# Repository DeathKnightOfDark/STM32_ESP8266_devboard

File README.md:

# STM32_ESP8266_devboard
Devboard, based on STM32 and ESP8266

This project about devboard, based on STM32F103C8T6 and ESP8266. They are connected with UART

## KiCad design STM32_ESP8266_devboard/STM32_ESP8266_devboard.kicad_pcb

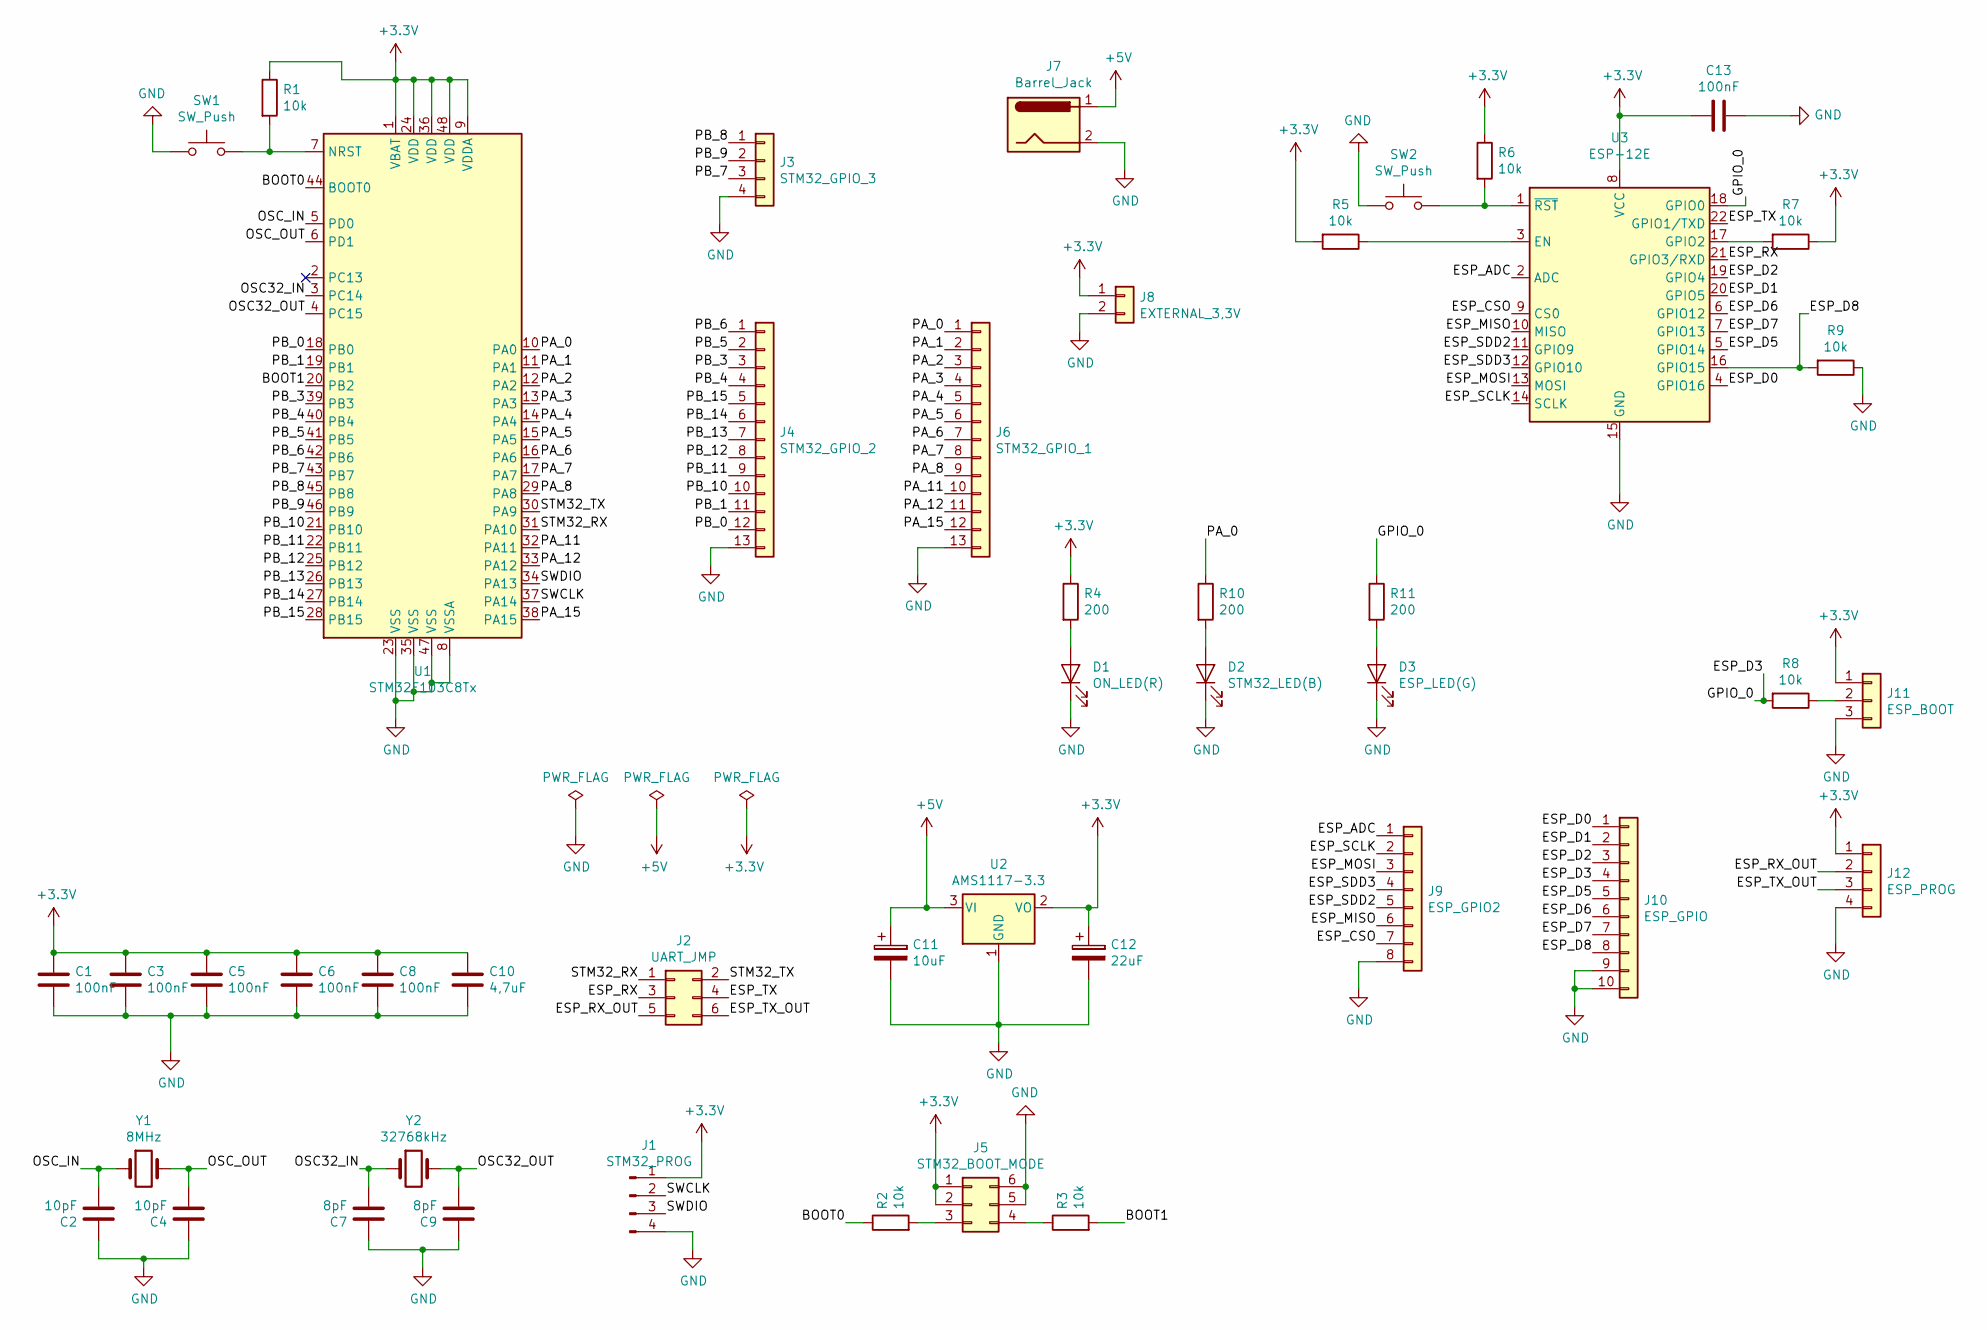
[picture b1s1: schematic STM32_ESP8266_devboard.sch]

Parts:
C1, C3, C5, C6, C8, C13: 100nF; C_0805_2012Metric
C2, C4: 10pF; C_0805_2012Metric
C7, C9: 8pF; C_0805_2012Metric
C10: 4,7uF; C_0805_2012Metric
C11: 10uF; CP_Radial_D5.0mm_P2.50mm
C12: 22uF; CP_Radial_D5.0mm_P2.00mm
D1: ON_LED(R); LED_0805_2012Metric
D2: STM32_LED(B); LED_0805_2012Metric
D3: ESP_LED(G); LED_0805_2012Metric
J1: STM32_PROG; PinHeader_1x04_P2.54mm_Vertical
J2: UART_JMP; PinHeader_2x03_P2.54mm_Vertical
J3: STM32_GPIO_3; PinHeader_1x04_P2.54mm_Vertical
J4: STM32_GPIO_2; PinHeader_1x13_P2.54mm_Vertical
J5: STM32_BOOT_MODE; PinHeader_2x03_P2.54mm_Vertical
J6: STM32_GPIO_1; PinHeader_1x13_P2.54mm_Vertical
J7: Barrel_Jack; BarrelJack_Horizontal
J8: EXTERNAL_3,3V; PinHeader_1x02_P2.54mm_Vertical
J9: ESP_GPIO2; PinHeader_1x08_P2.54mm_Vertical
J10: ESP_GPIO; PinHeader_1x10_P2.54mm_Vertical
J11: ESP_BOOT; PinHeader_1x03_P2.54mm_Vertical
J12: ESP_PROG; PinHeader_1x04_P2.54mm_Vertical
R1, R2, R3, R5, R6, R7, R8, R9: 10k; R_0805_2012Metric
R4, R10, R11: 200; R_0805_2012Metric
SW1, SW2: SW_Push; SW_PUSH_6mm
U1: STM32F103C8Tx; LQFP-48_7x7mm_P0.5mm
U2: AMS1117-3.3; SOT-223-3_TabPin2
U3: ESP-12E
Y1: 8MHz; Crystal_HC52-8mm_Vertical
Y2: 32768kHz; Crystal_DS26_D2.0mm_L6.0mm_Horizontal_1EP_style1

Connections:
+3V3: C1.2, C3.2, C5.2, C6.2, C8.2, C10.2, C12.1, C13.2, J1.1, J5.1, J5.2, J8.1, J11.1, J12.1, R1.1, R4.1, R5.2, R6.1, R7.1, U1.1 (VBAT), U1.9 (VDDA), U1.24 (VDD), U1.36 (VDD), U1.48 (VDD), U2.2 (VO), U3.8 (VCC); also elsewhere on the board
+5V: C11.1, J7.1, U2.3 (VI)
/BOOT0: R2.1, U1.44 (BOOT0)
/BOOT1: R3.2, U1.20 (PB2)
/ESP_ADC: J9.1, U3.2 (ADC)
/ESP_CSO: J9.7, U3.9 (CS0)
/ESP_D0: J10.1, U3.4 (GPIO16)
/ESP_D1: J10.2, U3.20 (GPIO5)
/ESP_D2: J10.3, U3.19 (GPIO4)
/ESP_D3: J10.4, R8.2, R11.1, U3.18 (GPIO0)
/ESP_D5: J10.5, U3.5 (GPIO14)
/ESP_D6: J10.6, U3.6 (GPIO12)
/ESP_D7: J10.7, U3.7 (GPIO13)
/ESP_D8: J10.8, R9.2, U3.16 (GPIO15)
/ESP_MISO: J9.6, U3.10 (MISO)
/ESP_MOSI: J9.3, U3.13 (MOSI)
/ESP_RX: J2.3, U3.21 (GPIO3/RXD)
/ESP_RX_OUT: J2.5, J12.2
/ESP_SCLK: J9.2, U3.14 (SCLK)
/ESP_SDD2: J9.5, U3.11 (GPIO9)
/ESP_SDD3: J9.4, U3.12 (GPIO10)
/ESP_TX: J2.4, U3.22 (GPIO1/TXD)
/ESP_TX_OUT: J2.6, J12.3
/OSC32_IN: C7.1, U1.3 (PC14), Y2.1
/OSC32_OUT: C9.1, U1.4 (PC15), Y2.2
/OSC_IN: C2.1, U1.5 (PD0), Y1.1
/OSC_OUT: C4.1, U1.6 (PD1), Y1.2
/PA_0: J6.1, R10.1, U1.10 (PA0)
/PA_1: J6.2, U1.11 (PA1)
/PA_2: J6.3, U1.12 (PA2)
/PA_3: J6.4, U1.13 (PA3)
/PA_4: J6.5, U1.14 (PA4)
/PA_5: J6.6, U1.15 (PA5)
/PA_6: J6.7, U1.16 (PA6)
/PA_7: J6.8, U1.17 (PA7)
/PA_8: J6.9, U1.29 (PA8)
/PA_11: J6.10, U1.32 (PA11)
/PA_12: J6.11, U1.33 (PA12)
/PA_15: J6.12, U1.38 (PA15)
/PB_0: J4.12, U1.18 (PB0)
/PB_1: J4.11, U1.19 (PB1)
/PB_3: J4.3, U1.39 (PB3)
/PB_4: J4.4, U1.40 (PB4)
/PB_5: J4.2, U1.41 (PB5)
/PB_6: J4.1, U1.42 (PB6)
/PB_7: J3.3, U1.43 (PB7)
/PB_8: J3.1, U1.45 (PB8)
/PB_9: J3.2, U1.46 (PB9)
/PB_10: J4.10, U1.21 (PB10)
/PB_11: J4.9, U1.22 (PB11)
/PB_12: J4.8, U1.25 (PB12)
/PB_13: J4.7, U1.26 (PB13)
/PB_14: J4.6, U1.27 (PB14)
/PB_15: J4.5, U1.28 (PB15)
/STM32_RX: J2.1, U1.31 (PA10)
/STM32_TX: J2.2, U1.30 (PA9)
/SWCLK: J1.2, U1.37 (PA14)
/SWDIO: J1.3, U1.34 (PA13)
GND: C1.1, C2.2, C3.1, C4.2, C5.1, C6.1, C7.2, C8.1, C9.2, C10.1, C11.2, C12.2, C13.1, D1.1 (K), D2.1 (K), D3.1 (K), J1.4, J3.4, J4.13, J5.5, J5.6, J6.13, J7.2, J8.2, J9.8, J10.9, J10.10, J11.3, J12.4, R9.1, SW1.1, SW2.1, U1.8 (VSSA), U1.23 (VSS), U1.35 (VSS), U1.47 (VSS), U2.1 (GND), U3.15 (GND); also elsewhere on the board
unnamed: D1.2 (A), R4.2
unnamed: D2.2 (A), R10.2
unnamed 61: D3.2 (A), R11.2; also elsewhere on the board
unnamed: J5.3, R2.2
unnamed: J5.4, R3.1
unnamed 64: J11.2, R8.1; also elsewhere on the board
unnamed: R1.2, SW1.2, U1.7 (NRST)
unnamed: R5.1, U3.3 (EN)
unnamed: R6.2, SW2.2, U3.1 (~RST)
unnamed: R7.2, U3.17 (GPIO2)

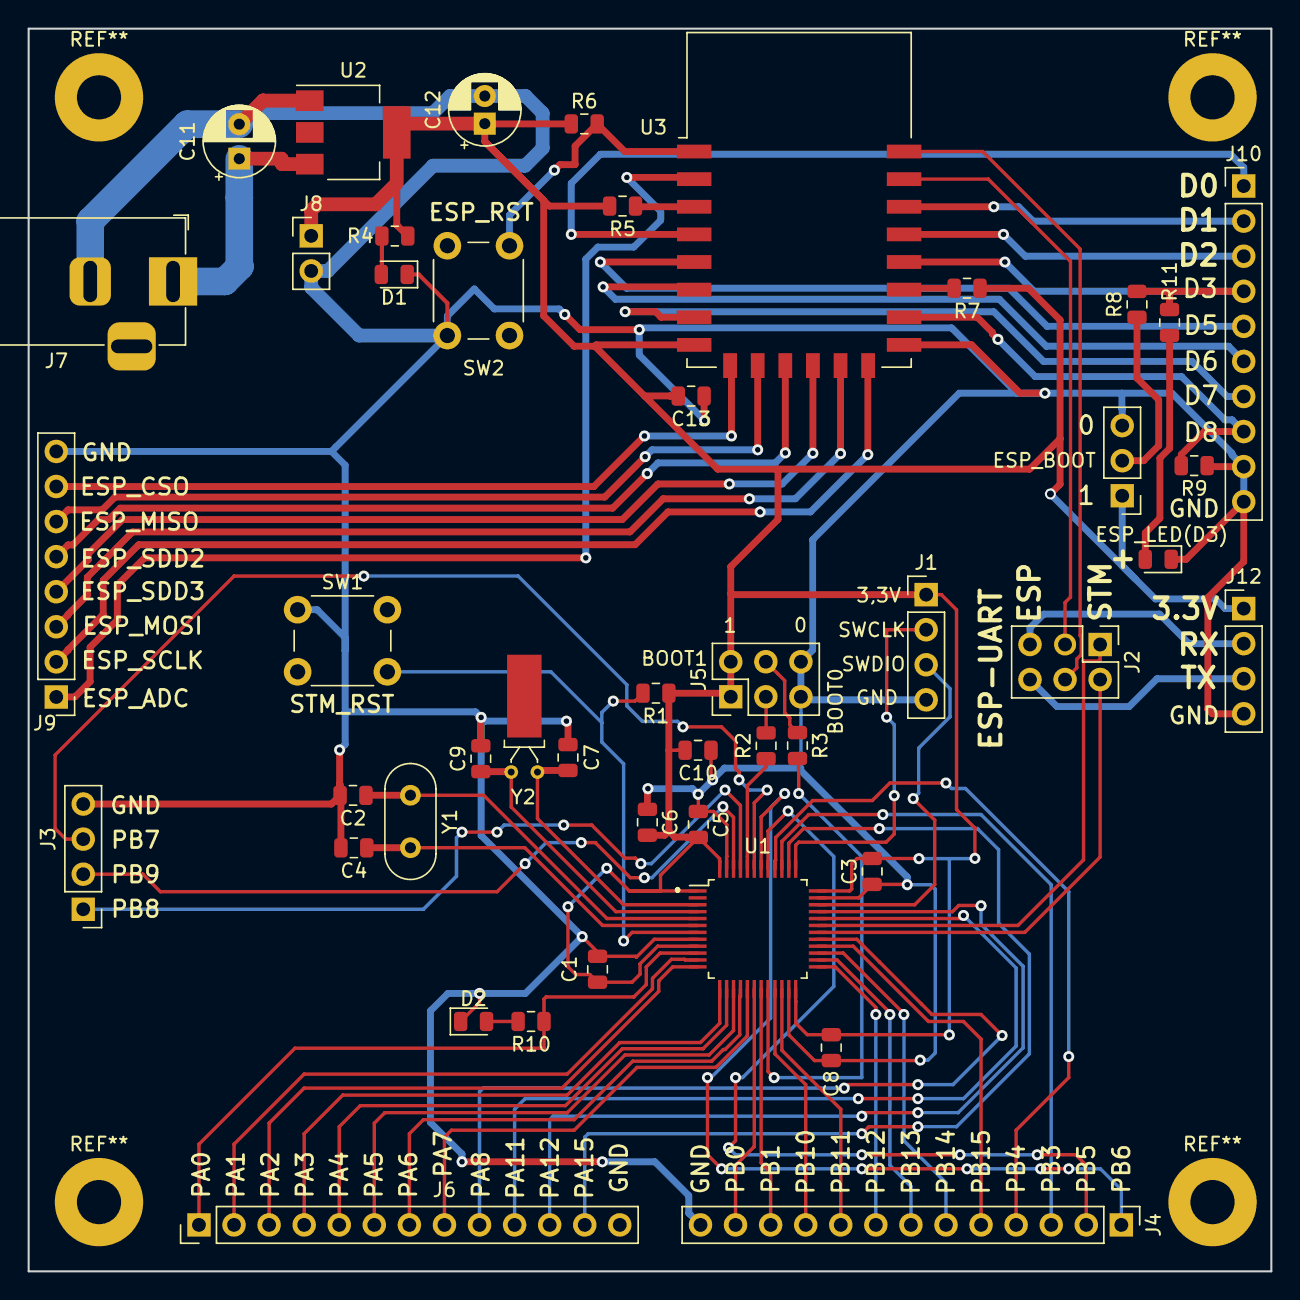
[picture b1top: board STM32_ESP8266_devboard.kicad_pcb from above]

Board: 2 copper layers, 90.0 x 90.0 mm, 46 parts (0 on the bottom side), 69 nets.

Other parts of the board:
ESP_BOOT: ESP_BOOT; PinHeader_1x03_P2.54mm_Vertical
ESP_LED(D3): ESP_LED(G); LED_0805_2012Metric

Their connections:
+3V3: ESP_BOOT.1; also elsewhere on the board
GND: ESP_BOOT.3, ESP_LED(D3).1; also elsewhere on the board
unnamed 61: ESP_LED(D3).2; also elsewhere on the board
unnamed 64: ESP_BOOT.2; also elsewhere on the board

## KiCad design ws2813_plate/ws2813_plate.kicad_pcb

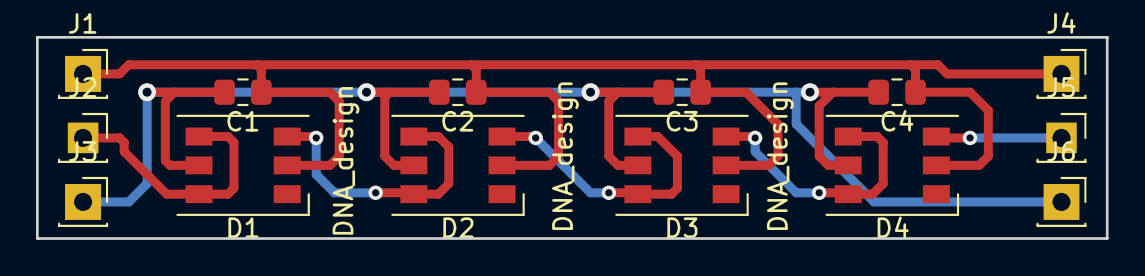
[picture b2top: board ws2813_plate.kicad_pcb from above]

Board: 2 copper layers, 59.4 x 11.2 mm, 14 parts (0 on the bottom side), 7 nets.

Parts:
C1, C2, C3, C4: 100nF; C_0805_2012Metric_Pad1.15x1.40mm_HandSolder
D1, D2, D3, D4: WS2813; LED_WS2812_PLCC6_5.0x5.0mm_P1.6mm
J1, J3, J4, J6: Conn_01x01; PinSocket_1x01_P2.54mm_Vertical
J2: DATA_IN; PinSocket_1x01_P2.54mm_Vertical
J5: DATA_OUT; PinSocket_1x01_P2.54mm_Vertical

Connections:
+5V: C1.1, C2.1, C3.1, C4.1, D1.2, D2.2, D3.2, D4.2, J1.1, J4.1
/DATA: D1.4, D1.6, J2.1
GND: C1.2, C2.2, C3.2, C4.2, D1.5, D2.5, D3.5, D4.5, J3.1, J6.1
unnamed: D1.3, D2.4, D2.6
unnamed: D2.3, D3.4, D3.6
unnamed: D3.3, D4.4, D4.6
unnamed: D4.3, J5.1

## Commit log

2020-08-24 Initial commut.
2020-08-24 Initial commit.
2020-08-24 Another commit
2020-08-25 Another commit, not final
2020-08-25 Another commit #2
2020-08-27 another one commit
2020-08-27 another one commit#3
2020-08-28 Final principal scheme
2020-08-31 Begin PCB
2020-09-02 Another day another commit
2020-09-09 Another one commit, not final
2020-09-10 Все хуйня, разводи плату по новой
2020-09-17 Another one
2020-09-18 Final version, add logos
2020-09-21 Pre-final pcb
2020-10-12 final commit, v.1.0.0
